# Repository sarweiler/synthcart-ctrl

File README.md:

# Synthcart Ctrl

Synthcart Ctrl is a controller for the Atari 2600 synthesizer [Synthcart](http://www.qotile.net/synth.html) by Paul Slocum. It's basically two Atari keyboard controller circuits on a single PCB.

## Building Synthcart Ctrl

Building a Synthcart Ctrl is a very easy and beginner-friendly soldering project.

### PCB

Download the [synthcart-ctrl-gerbers.zip](https://github.com/sarweiler/synthcart-ctrl/releases/latest/download/synthcart-ctrl-gerbers.zip) file for the latest release, upload the zip archive to a PCB manufacturer of your choice, and order a PCB. Usually the default settings for the PCBs are okay – just choose a color for the solder mask that you like, if you dont want the standard PCB-green.

### Parts

* Four 4.7kOhm resistors.
* 24 Cherry MX switches of your choice, preferably of the PCB-mount variant (with fixation pins, [these, for example](https://www.mouser.com/ProductDetail/540-MX1A-11NW)). Non-PCB-mount switches (frame mount, without fixation pins) will work, too, but you will have to be careful to align them correctly when soldering.
* Two female DB9 connectors of the PCB-mount variant with mounting pins ([these](https://www.mouser.com/ProductDetail/571-2311765-1), [these](https://www.reichelt.de/d-sub-buchse-9-polig-gewinkelt-rm-9-4-gedr-d-sub-bu-09gwc-p113921.html), or any connector with similar measurements will work).
* 24 Cherry MX compatible keycaps of your choice. (I used [these](https://www.aliexpress.com/item/32987364794.html?spm=a2g0s.9042311.0.0.27424c4dBs286T) in the "blank" variant.)
* Two DB9 extension cables for connecting the controller to the Atari.
* 4 rubber feet

### Soldering

* Start by soldering the four 4.7k resistors.
* Solder the two female DB9 connectors.
* Solder all 24 Cherry MX switches. If you're using non-PCB-mount switches be careful to align them correctly.
* Install your keycaps on the switches.
* Add the rubber feet to the bottom of the PCB to avoid shorts when using the controller on conductive surfaces.
* Done!

## Using Synthcart Ctrl

Using the controller is pretty straight forward: Connect the left port of your controller to the left joystick port on the Atari and the right port to the right joystick port on the Atari using two DB9 extension cables.

Use the two sides of the controller like you would use two Atari keyboard controllers to control Synthcart.

For information on how to use Synthcart, check out the [Synthcart](http://www.qotile.net/synth.html) manual.

## Disclaimer

Build and use Synthcart Ctrl at your own risk. I cannot be held responsible for damage caused to your devices, yourself or others.

## License

This work is licensed under [CC-BY-SA 4.0](http://creativecommons.org/licenses/by-sa/4.0/).

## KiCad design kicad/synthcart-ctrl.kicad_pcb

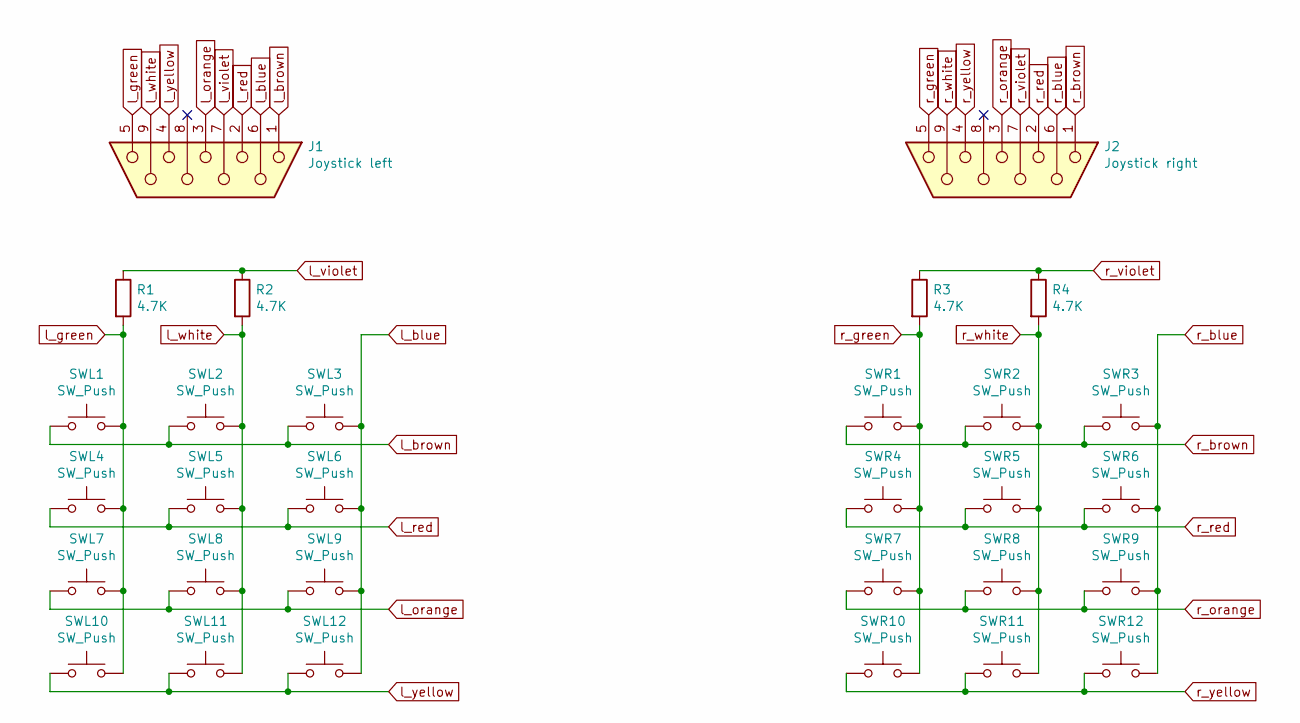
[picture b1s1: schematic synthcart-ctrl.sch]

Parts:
J1: Joystick left; DSUB-9_Female_Horizontal_P2.77x2.84mm_EdgePinOffset9.90mm_H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
J2: Joystick right; DSUB-9_Female_Horizontal_P2.77x2.84mm_EdgePinOffset9.90mm_H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
R1, R2, R3, R4: 4.7K; R_Axial_DIN0207_L6.3mm_D2.5mm_P10.16mm_Horizontal
SWL1, SWL2, SWL3, SWL4, SWL5, SWL6, SWL7, SWL8, SWL9, SWL10, SWL11, SWL12: SW_Push; SW_Cherry_MX_1.00u_PCB
SWR1, SWR2, SWR3, SWR4, SWR5, SWR6, SWR7, SWR8, SWR9, SWR10, SWR11, SWR12: SW_Push; SW_Cherry_MX_1.00u_PCB

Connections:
l_blue: J1.6, SWL3.2, SWL6.2, SWL9.2, SWL12.2
l_brown: J1.1, SWL1.1, SWL2.1, SWL3.1
l_green: J1.5, R1.2, SWL1.2, SWL4.2, SWL7.2, SWL10.2; also elsewhere on the board
l_orange: J1.3, SWL7.1, SWL8.1, SWL9.1
l_red: J1.2, SWL4.1, SWL5.1, SWL6.1
l_violet: J1.7, R1.1, R2.1; also elsewhere on the board
l_white: J1.9, R2.2, SWL2.2, SWL5.2, SWL8.2, SWL11.2
l_yellow: J1.4, SWL10.1, SWL11.1, SWL12.1
r_blue: J2.6, SWR3.2, SWR6.2, SWR9.2, SWR12.2
r_brown: J2.1, SWR1.1, SWR2.1, SWR3.1
r_green: J2.5, R3.2, SWR1.2, SWR4.2, SWR7.2, SWR10.2
r_orange: J2.3, SWR7.1, SWR8.1, SWR9.1
r_red: J2.2, SWR4.1, SWR5.1, SWR6.1
r_violet: J2.7, R3.1, R4.1
r_white: J2.9, R4.2, SWR2.2, SWR5.2, SWR8.2, SWR11.2
r_yellow: J2.4, SWR10.1, SWR11.1, SWR12.1

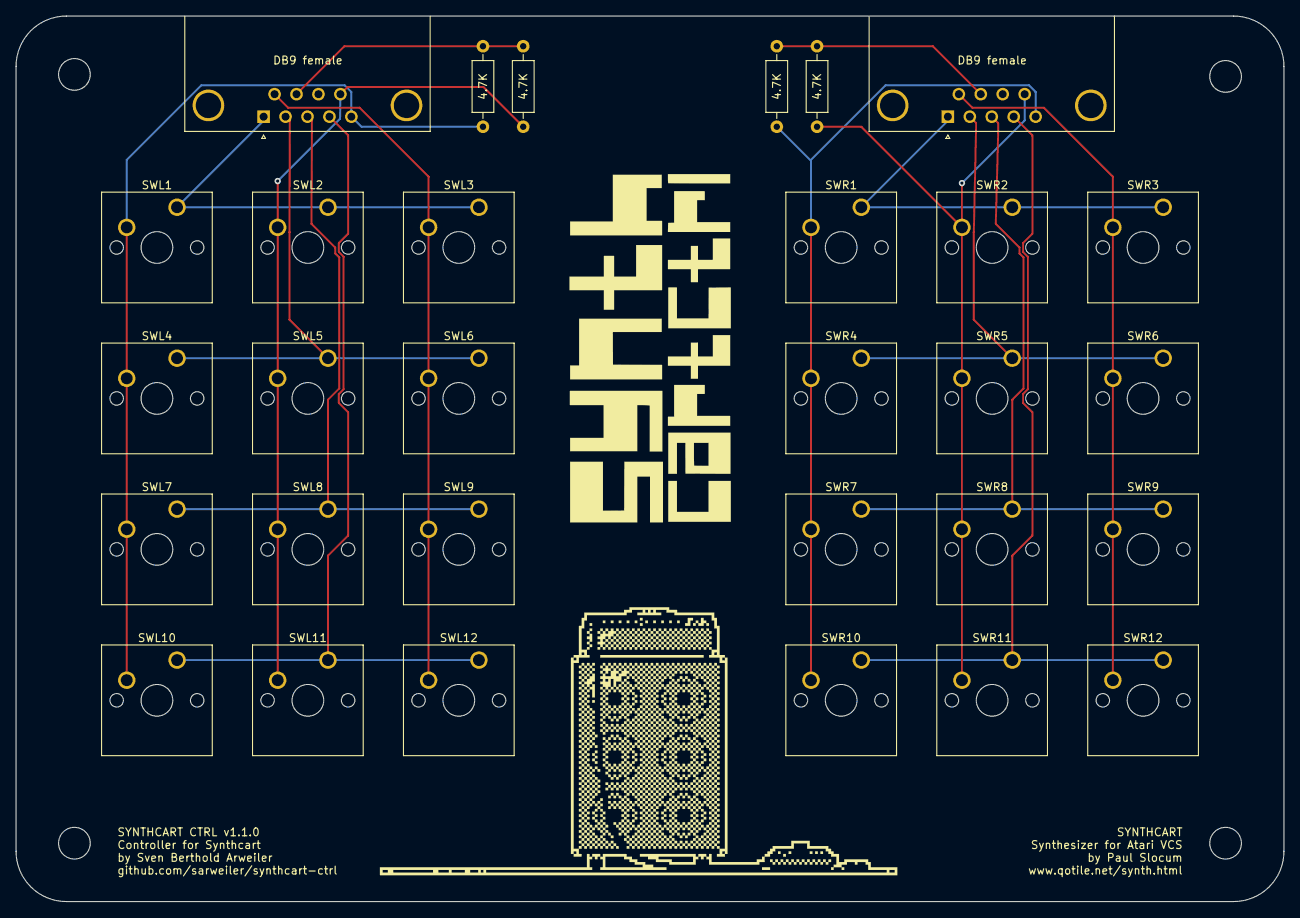
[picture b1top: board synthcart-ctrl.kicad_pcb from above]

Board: 2 copper layers, 160.0 x 111.8 mm, 30 parts (0 on the bottom side), 16 nets.

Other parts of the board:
Re: 4.7K; R_Axial_DIN0207_L6.3mm_D2.5mm_P10.16mm_Horizontal

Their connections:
l_green: Re.2; also elsewhere on the board
l_violet: Re.1; also elsewhere on the board

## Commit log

2020-08-27 add Kicad files
2020-08-27 add license
2020-08-27 add .gitignore
2020-08-27 add image
2020-08-27 add PCB artwork to README
2020-08-27 update photo
2020-08-28 update README with link to gerbers.zip for the latest release
2020-08-28 rename license file
2020-11-01 remove backup file
2020-11-01 version 1.1.0 changes
    - move resisitors for left DB9 port to the right of the port
    - add 4mm mounting holes
    - pixel art without dithering
2020-11-13 new image for version 1.1.0
2021-02-28 remove LICENSE.txt
2021-02-28 update README with CC license information
